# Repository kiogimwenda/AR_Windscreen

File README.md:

# AR_Windscreen

**AR-Assisted Semi-Autonomous Driving System** — a retrofit driver-support platform centered on
precision, sensor-fused AR navigation and force-limited collision-avoidance braking.

The system fuses camera, LiDAR, GPS, IMU and OBD-II data into a real-time model of the road ahead,
renders that understanding as a road-locked augmented-reality overlay on the vehicle's forward view,
and — through a dedicated STM32 sensor/actuator hub — can trigger indicators, lights and a
force-limited brake-pedal actuation when a collision risk crosses a defined threshold.

## Safety

This project has one hard rule that overrides every other design consideration:

> The brake actuator must never be able to exert more force than a driver's foot can override, must
> never disconnect or block the driver's own pedal linkage, and must default to fully released/inert
> on any fault, timeout, link loss, or ambiguous state.

The host laptop never drives actuation hardware directly — it sends a bounded *request* to the hub,
and the hub's firmware enforces the real ceiling, independent of host software correctness. A
physical kill switch removes actuator power independent of software, and the hub's watchdog releases
the actuator within 200 ms of host link loss.

See `docs/BUILD_GUIDE.md` Part 0 and Part 9 for the full safety design.

## Layout

| Path | Contents |
|---|---|
| `docs/` | Build guide, design decisions, progress log, architecture, report and presentation sources |
| `firmware/sensor_actuator_hub/` | STM32 / FreeRTOS firmware — the only component with direct electrical access to the vehicle |
| `host/` | Laptop-side C++ application: perception, fusion, decision, navigation, rendering |
| `tools/bench_rig/` | Bench-test instrumentation and offline replay harness |
| `cmake/` | Custom CMake find-modules (TensorRT) |

## Documentation

- `docs/BUILD_GUIDE.md` — the full implementation specification this project is built from
- `docs/decisions.md` — running log of implementation choices made under ambiguity
- `docs/progress-log.md` — dated, per-task record of work completed
- `docs/architecture/system-architecture.md` — as-built architecture

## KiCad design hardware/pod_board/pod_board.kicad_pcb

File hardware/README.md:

# Hardware

The custom hardware of the two-box hub: `docs/BUILD_GUIDE.md` Part 4.8 is the design, Part 14
Phase 12B the plan.

| Directory | Contents | Status (2026-10-06) |
|---|---|---|
| `gen/` | The board descriptions, the power board's drawing, and the tools that turn them into KiCad files and check them | Done |
| `pod_board/` | KiCad 10 project: STM32F405RGT6, 8 MHz crystal, USB-C, diode-OR'd 5 V to 3.3 V, IMU / GNSS / gesture / SWD / ELM327 headers, status LEDs, DB-25 with series resistors and input filters. 4-layer. | Schematic done, ERC clean, cross-checked; **placed** (77 parts, 0 DRC errors, matches the schematic); **routing to do** (`LAYOUT_GUIDE.md`) |
| `power_board/` | KiCad 10 project: 12 V fuse, TVS and reverse-polarity diode; TPS54360 5 V (TI reference design); 3.3 V; 74HCT244 buffer; BTS7960 and ACS712 module headers; magnet and relay MOSFETs with flyback diodes; fail-safe pull-downs; SN65HVD230 CAN; presence MOSFET; PC817 brake-light input; terminals for the kill relay, E-stop, relays, actuator, LiDAR and OBD lead; DB-25. 2-layer, 2 oz. | Schematic done, ERC clean, cross-checked; **placed** (82 parts, 0 DRC errors, matches the schematic); **routing to do** (`LAYOUT_GUIDE.md`) |
| `enclosures/` | OpenSCAD: LiDAR roof mount, power-box chassis and box drilling templates; shared board outlines (`common/boards.scad`). See its README. | LiDAR mount and power box designed; pod, E-stop and gesture puck wait for the parts and the car |

Each board folder also has `<board>.pdf` (the schematic, for reading without KiCad) and
`<board>_bom.csv` (parts grouped by value and footprint).

## How the schematics are made and checked

```bash
hardware/gen/check.sh
```
1. `gen/generate.py` writes both `.kicad_sch` files from `gen/pod_board.py` and
   `gen/power_board.py`. Each part names its KiCad symbol, footprint and value and maps **pin
   numbers to net names**; the generator copies the real library symbols in.
   - **Both boards are drawn (2026-10-07).** `gen/power_board_drawing.py` places every part by hand
     on one of eight function sheets (12 V input, 5 V converter, 3.3 V and feeds, brake actuator,
     signal relays, CAN, status inputs, DB-25), and `gen/kisheet.py` routes **real wires** between
     the pins, puts power symbols on power pins, names each net with a label, and draws a root
     sheet that is the **block diagram**: one box per sheet, the cable signals wired between them.
     Open `power_board.kicad_pro`, start on the block diagram, double-click a box to enter it.
     `gen/pod_board_drawing.py` does the same for the pod: power, USB-C, the MCU (in the middle,
     every pin straight out to a port), sensors and local connectors, status LEDs, and the cable
     interface (series resistors, pull-ups and filters fanning in to the DB-25 without a crossing).
2. KiCad's ERC must report **0 violations**. For each drawn board, the label-only version is also
   generated (in a scratch directory) and `gen/compare_nets.py` requires the two netlists to be
   **identical**: same parts, values and footprints, every net joining the same pins under the
   same name. The drawing therefore cannot have changed the circuit. The wire router never lets two
   nets touch; a wire may only cross another at right angles over a plain run (no dot, no
   connection), never at a bend, pin or junction.
3. `gen/check_nets.py` reads the exported netlists and verifies, against the sources of truth:
   - every pin in `firmware/.../Config.h` is on the right STM32 pin of the pod board;
   - every DB-25 pin on both boards matches the table in BUILD_GUIDE 4.8.3 (parsed from the guide);
   - pod: each cable line passes through a series resistor; inputs read safe when unplugged;
   - power board: every pod-driven line is pulled to its safe state (Part 4.8.4's rule);
   - no misspelt single-connection nets; no pin in two nets (two parts sharing a reference,
     which KiCad's ERC does not report); every footprint exists in KiCad's library.

   It was tested by breaking the design on purpose (a relay moved to the wrong MCU pin, a
   pull-down removed, two cable pins swapped); each was caught.

**Change the design in `gen/*.py`, never only in KiCad's editor**, then run `check.sh`. Edits made
only in the `.kicad_sch` are overwritten by the next generation. (Once layout starts, the
schematic can be frozen and edited in KiCad directly; then stop regenerating and keep running the
netlist check: export the netlist from KiCad and run `check_nets.py` on it.)

## Choices made during schematic capture (see also decisions.md)

- **Reverse polarity: a B560C Schottky, not a P-MOSFET.** SOT-23 P-MOSFETs are rated −30 V, too
  close to the TVS's ~39 V clamp. The diode drops ~0.6 V (~1 W at 2 A) and needs no gate circuit.
- **5 V converter: TI's TPS54360 reference design, unchanged** (datasheet SLVSBB4G, Figure 34):
  600 kHz, 8.2 µH, B560C, 2 × 47 µF, compensation 13.0 k / 6800 p / 39 p, start 8 V / stop 6.25 V.
  Copying a validated design is the right call for a first board; it is rated well beyond our
  ~1 A load.
- **Relays and magnet: logic-level MOSFETs driven straight from the cable lines** (AO3400A turns
  fully on at 2.5 V); the 74HCT244 buffers only the BTS7960 module's three 5 V inputs.
- **Back-powering:** each pod output has a 1 k series resistor (330 Ω on CAN_TX for its 500 kbit/s
  edges), so a pod running on USB cannot push more than ~3 mA per line into an unpowered box.
- **Module headers are placeholders for breakouts** (BNO085, NEO-M8N): the pin order on `J2` and
  `J3` of the pod board must be matched to the actual breakouts bought **before layout**.

## What remains for Phase 12B (Ian's work)

**Both boards are placed (2026-10-08): routing, finishing and ordering remain, step by step in
[`LAYOUT_GUIDE.md`](LAYOUT_GUIDE.md).** `gen/layout.sh` built each `.kicad_pcb` from the board
descriptions: every footprint from KiCad's library, each pad on its net (from KiCad's own
netlist), placed per `gen/placement.py` (each position with its reason, listed in
`<board>/placement.md`, pictured in `<board>/placement.png`), linked to its schematic symbol, the
net classes and fab rules (`gen/pcb_rules.py`, track widths from IPC-2221) and the copper planes
in place; then KiCad's DRC with the schematic-parity check: 0 errors, exact parity. The schematic
generator now gives every object a deterministic id, so the links survive regeneration and the
files only change when the design does.

The notes below are the layout principles the placement follows (and the guide expands).

**Pod board (4-layer: signal / ground / power / signal).**
- Decoupling capacitors (C3–C9) at their VDD pins, each with its own via to the ground plane.
  VCAP capacitors (C10, C11) right at pins 31 and 47.
- Crystal (Y1, C12, C13) within ~5 mm of PH0/PH1, nothing routed underneath, guard with ground.
- USB D+/D− as a matched pair (~90 Ω differential), short, the ESD chip (U4) right at the socket.
- The GNSS breakout at the board edge that faces the glass, away from the MCU and the USB; keep
  the ground plane unbroken under it.
- The IMU breakout on standoffs at a fixed, known orientation (record it: Part 12.2.2 calibrates
  it, but a sensible starting orientation makes the calibration easy to check).
- DB-25 at one end, the series resistors and input filters right behind it.
- Status LEDs on the edge that faces the driver.

**Power board (2-layer, 2 oz copper).**
- The TPS54360's power loop is the critical path: input capacitors (C21, C22), the IC, the catch
  diode (D13) and the inductor (L1) as close together as possible, the SW node small (it is the
  board's noise source), the feedback divider (R44, R45) away from L1 and the SW node. Follow the
  datasheet's layout example (its "Layout" section) closely.
- Wide traces or pours for the 12 V input, the actuator rail (ACT_12V) and the relay coils' +12 V;
  the actuator's heavy current itself runs in wire on the BTS7960 module, not on this board.
- Fuse holders and terminal blocks along the edges, grouped by what they connect to (12 V in,
  actuator side, car-wiring side).
- The SN65HVD230 and its ESD diode (D20) right at the OBD terminal block.
- The 10 k pull-downs close to the DB-25, so the lines are defined as soon as they enter the board.

**Then:** DRC clean, a 1:1 paper print to check every footprint against the real part, Gerbers,
order (JLCPCB / PCBWay), assemble, and bring up with Part 4.7 before the bench gate is re-run on
this hardware (three consecutive passes of all six items).

## Board outlines: the one constraint shared with the enclosures

```bash
python3 hardware/gen/outlines.py           # --force to overwrite a .kicad_pcb already being laid out
```
`gen/outlines.py` holds each board's size, corner radius, M3 mounting holes and the positions of
its edge connectors (DB-25, USB-C, fuses, terminal blocks, LEDs, headers). It writes the starter
`<board>.kicad_pcb` (outline on Edge.Cuts, hole positions on User.Drawings, connector boxes on
User.Comments: place H1–H4 and the connectors on them) and `enclosures/common/boards.scad`, which
the enclosure models include. Pod board 70 × 53 mm, 4 layers; power board 95 × 66 mm, 2 layers (compacted 2026-10-08 from 80 × 55 and 110 × 80; the power board 5 mm wider again on 2026-10-09 for its silkscreen labels).
If a layout needs a change, change it there and regenerate both. The starter files passed KiCad's
DRC with no errors.

**Placed and routed (2026-10-09):** `gen/layout.sh` places every part (`gen/placement.py`, with
each position's reason and the silkscreen names), `gen/route.sh` routes both boards to the
specification and keeps a board only with 0 unconnected, 0 DRC errors and exact schematic parity,
and `gen/routespec.sh` checks what the DRC cannot (planes, crystal, converter, widths). How it was
done and how to review it: `LAYOUT_GUIDE.md`.

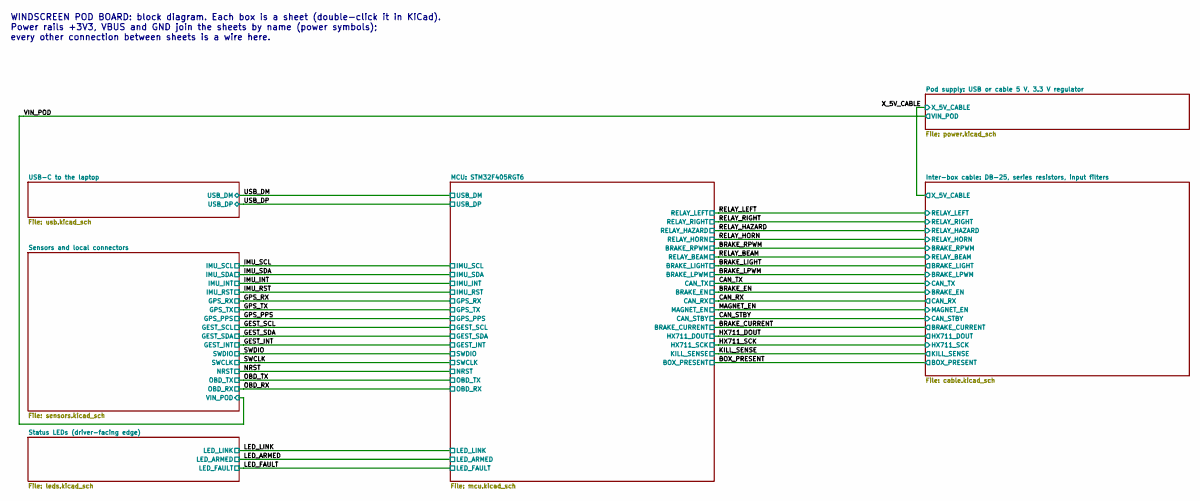
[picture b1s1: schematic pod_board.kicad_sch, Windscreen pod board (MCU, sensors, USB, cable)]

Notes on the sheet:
WINDSCREEN POD BOARD: block diagram. Each box is a sheet (double-click it in KiCad). Power rails +3V3, VBUS and GND join the sheets by name (power symbols); every other connection between sheets is a wire here.

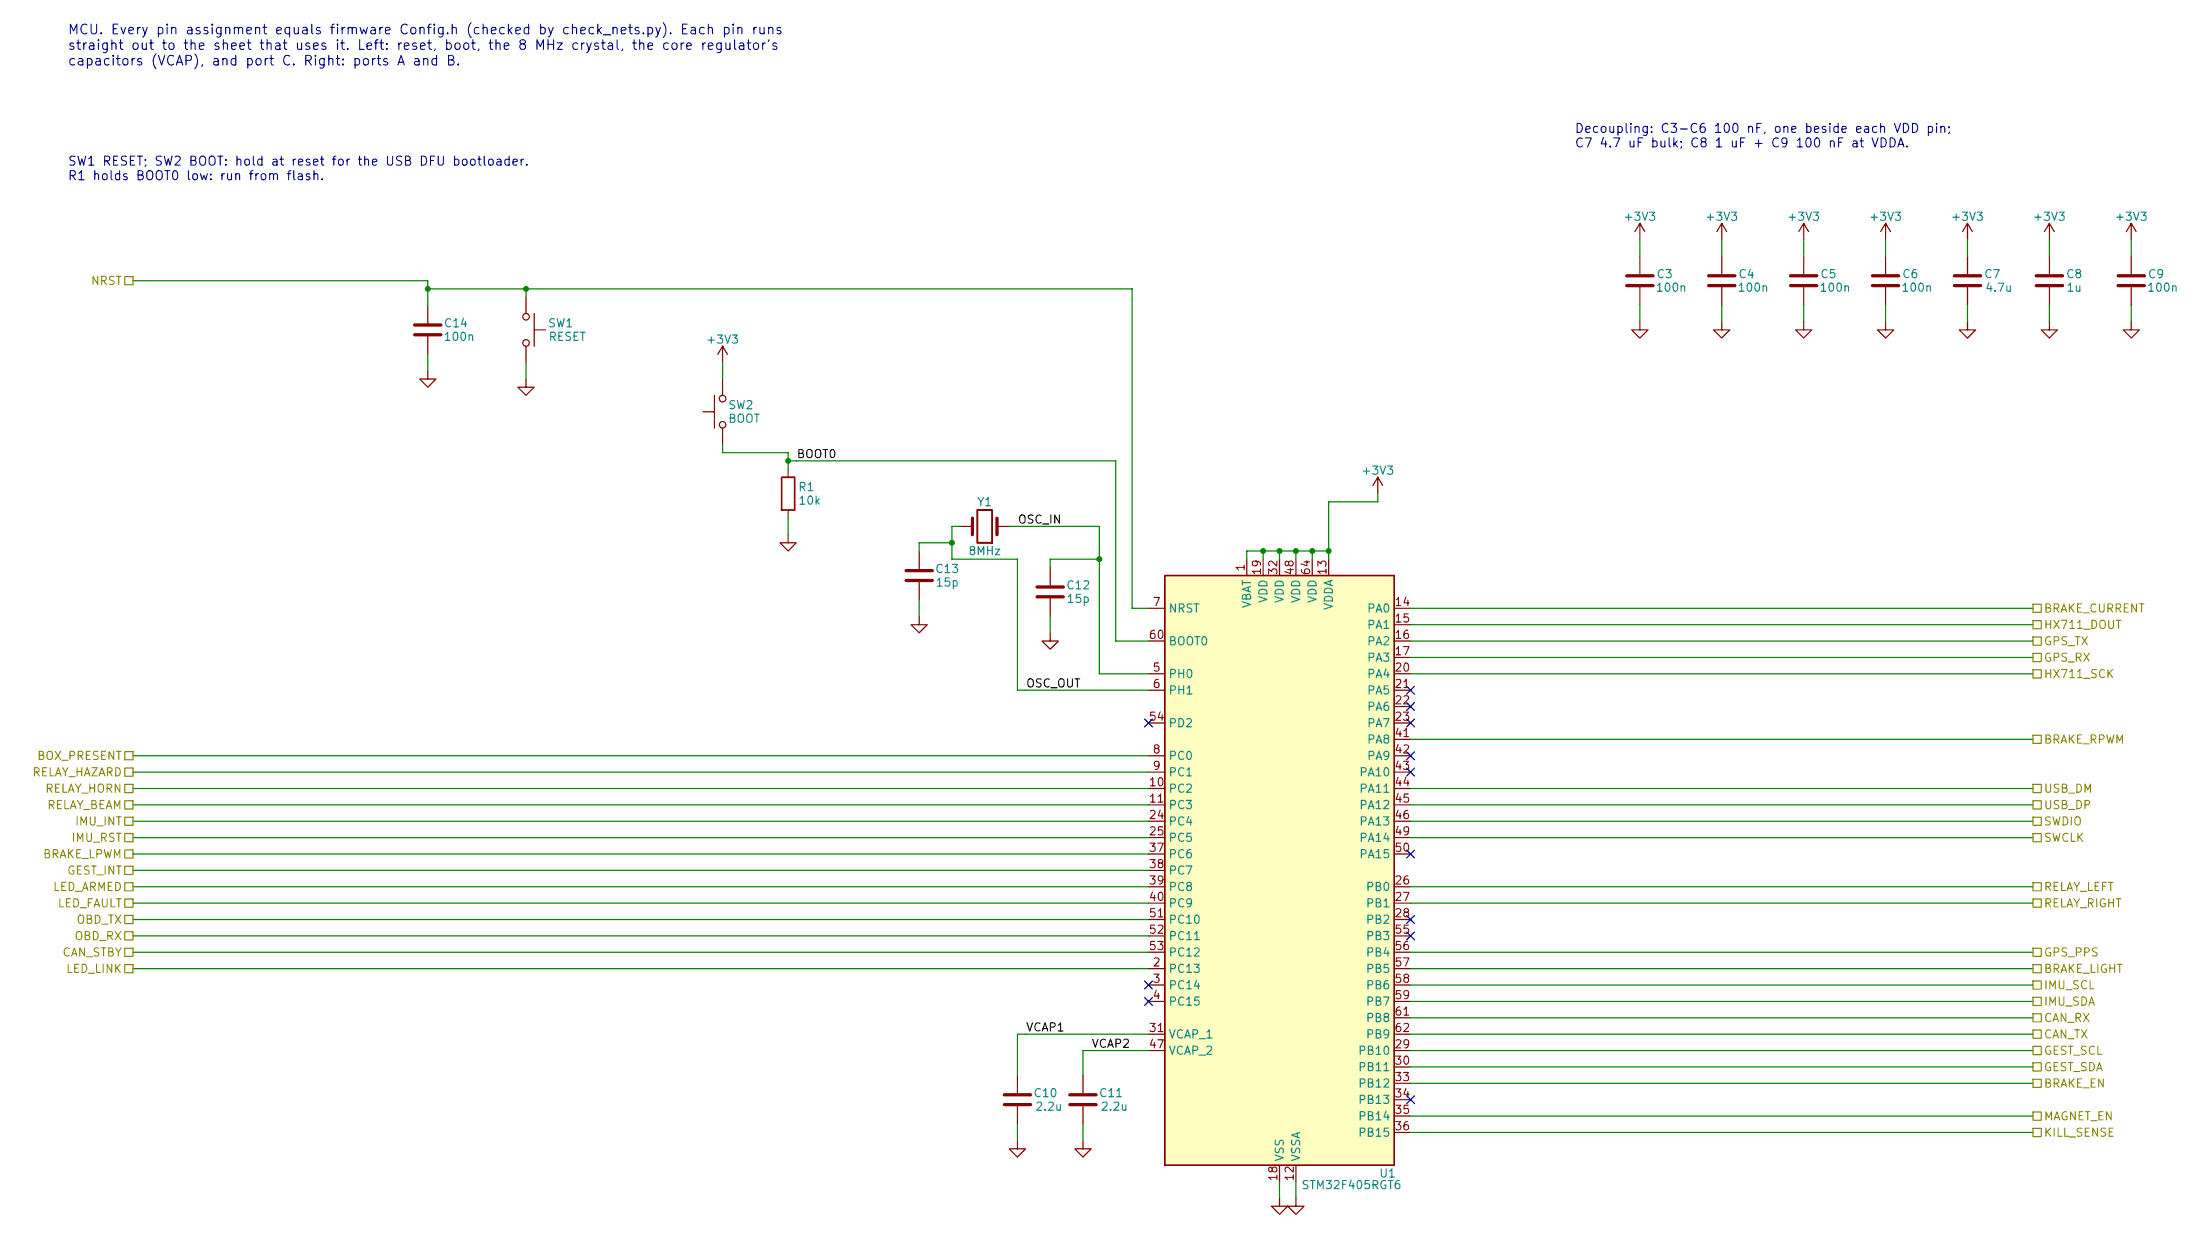
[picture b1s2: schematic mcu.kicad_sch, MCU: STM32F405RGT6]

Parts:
C3, C4, C5, C6, C9, C14: 100n; C_0805_2012Metric
C7: 4.7u; C_1206_3216Metric
C8: 1u; C_0805_2012Metric
C10, C11: 2.2u; C_0805_2012Metric
C12, C13: 15p; C_0805_2012Metric
R1: 10k; R_0805_2012Metric
SW1: RESET; SW_SPST_EVQP7C
SW2: BOOT; SW_SPST_EVQP7C
U1: STM32F405RGT6; LQFP-64_10x10mm_P0.5mm
Y1: 8MHz; Crystal_SMD_HC49-SD

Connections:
+3V3: C3.1, C4.1, C5.1, C6.1, C7.1, C8.1, C9.1, SW2.2, U1.1 (VBAT), U1.13 (VDDA), U1.19 (VDD), U1.32 (VDD), U1.48 (VDD), U1.64 (VDD); also elsewhere on the board
/BOX_PRESENT: U1.8 (PC0); also elsewhere on the board
/BRAKE_CURRENT: U1.14 (PA0); also elsewhere on the board
/BRAKE_EN: U1.33 (PB12); also elsewhere on the board
/BRAKE_LIGHT: U1.57 (PB5); also elsewhere on the board
/BRAKE_LPWM: U1.37 (PC6); also elsewhere on the board
/BRAKE_RPWM: U1.41 (PA8); also elsewhere on the board
/CAN_RX: U1.61 (PB8); also elsewhere on the board
/CAN_STBY: U1.53 (PC12); also elsewhere on the board
/CAN_TX: U1.62 (PB9); also elsewhere on the board
/GEST_INT: U1.38 (PC7); also elsewhere on the board
/GEST_SCL: U1.29 (PB10); also elsewhere on the board
/GEST_SDA: U1.30 (PB11); also elsewhere on the board
/GPS_PPS: U1.56 (PB4); also elsewhere on the board
/GPS_RX: U1.17 (PA3); also elsewhere on the board
/GPS_TX: U1.16 (PA2); also elsewhere on the board
/HX711_DOUT: U1.15 (PA1); also elsewhere on the board
/HX711_SCK: U1.20 (PA4); also elsewhere on the board
/IMU_INT: U1.24 (PC4); also elsewhere on the board
/IMU_RST: U1.25 (PC5); also elsewhere on the board
/IMU_SCL: U1.58 (PB6); also elsewhere on the board
/IMU_SDA: U1.59 (PB7); also elsewhere on the board
/KILL_SENSE: U1.36 (PB15); also elsewhere on the board
/LED_ARMED: U1.39 (PC8); also elsewhere on the board
/LED_FAULT: U1.40 (PC9); also elsewhere on the board
/LED_LINK: U1.2 (PC13); also elsewhere on the board
/MAGNET_EN: U1.35 (PB14); also elsewhere on the board
/MCU: STM32F405RGT6/BOOT0: R1.1, SW2.1, U1.60 (BOOT0)
/MCU: STM32F405RGT6/OSC_IN: C12.1, U1.5 (PH0), Y1.1
/MCU: STM32F405RGT6/OSC_OUT: C13.1, U1.6 (PH1), Y1.2
/MCU: STM32F405RGT6/VCAP1: C10.1, U1.31 (VCAP_1)
/MCU: STM32F405RGT6/VCAP2: C11.1, U1.47 (VCAP_2)
/NRST: C14.1, SW1.1, U1.7 (NRST); also elsewhere on the board
/OBD_RX: U1.52 (PC11); also elsewhere on the board
/OBD_TX: U1.51 (PC10); also elsewhere on the board
/RELAY_BEAM: U1.11 (PC3); also elsewhere on the board
/RELAY_HAZARD: U1.9 (PC1); also elsewhere on the board
/RELAY_HORN: U1.10 (PC2); also elsewhere on the board
/RELAY_LEFT: U1.26 (PB0); also elsewhere on the board
/RELAY_RIGHT: U1.27 (PB1); also elsewhere on the board
/SWCLK: U1.49 (PA14); also elsewhere on the board
/SWDIO: U1.46 (PA13); also elsewhere on the board
/USB_DM: U1.44 (PA11); also elsewhere on the board
/USB_DP: U1.45 (PA12); also elsewhere on the board
GND: C3.2, C4.2, C5.2, C6.2, C7.2, C8.2, C9.2, C10.2, C11.2, C12.2, C13.2, C14.2, R1.2, SW1.2, U1.12 (VSSA), U1.18 (VSS), U1.63 (VSS); also elsewhere on the board

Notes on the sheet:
MCU. Every pin assignment equals firmware Config.h (checked by check_nets.py). Each pin runs straight out to the sheet that uses it. Left: reset, boot, the 8 MHz crystal, the core regulator's capacitors (VCAP), and port C. Right: ports A and B.
Decoupling: C3-C6 100 nF, one beside each VDD pin; C7 4.7 uF bulk; C8 1 uF + C9 100 nF at VDDA.
SW1 RESET; SW2 BOOT: hold at reset for the USB DFU bootloader. R1 holds BOOT0 low: run from flash.

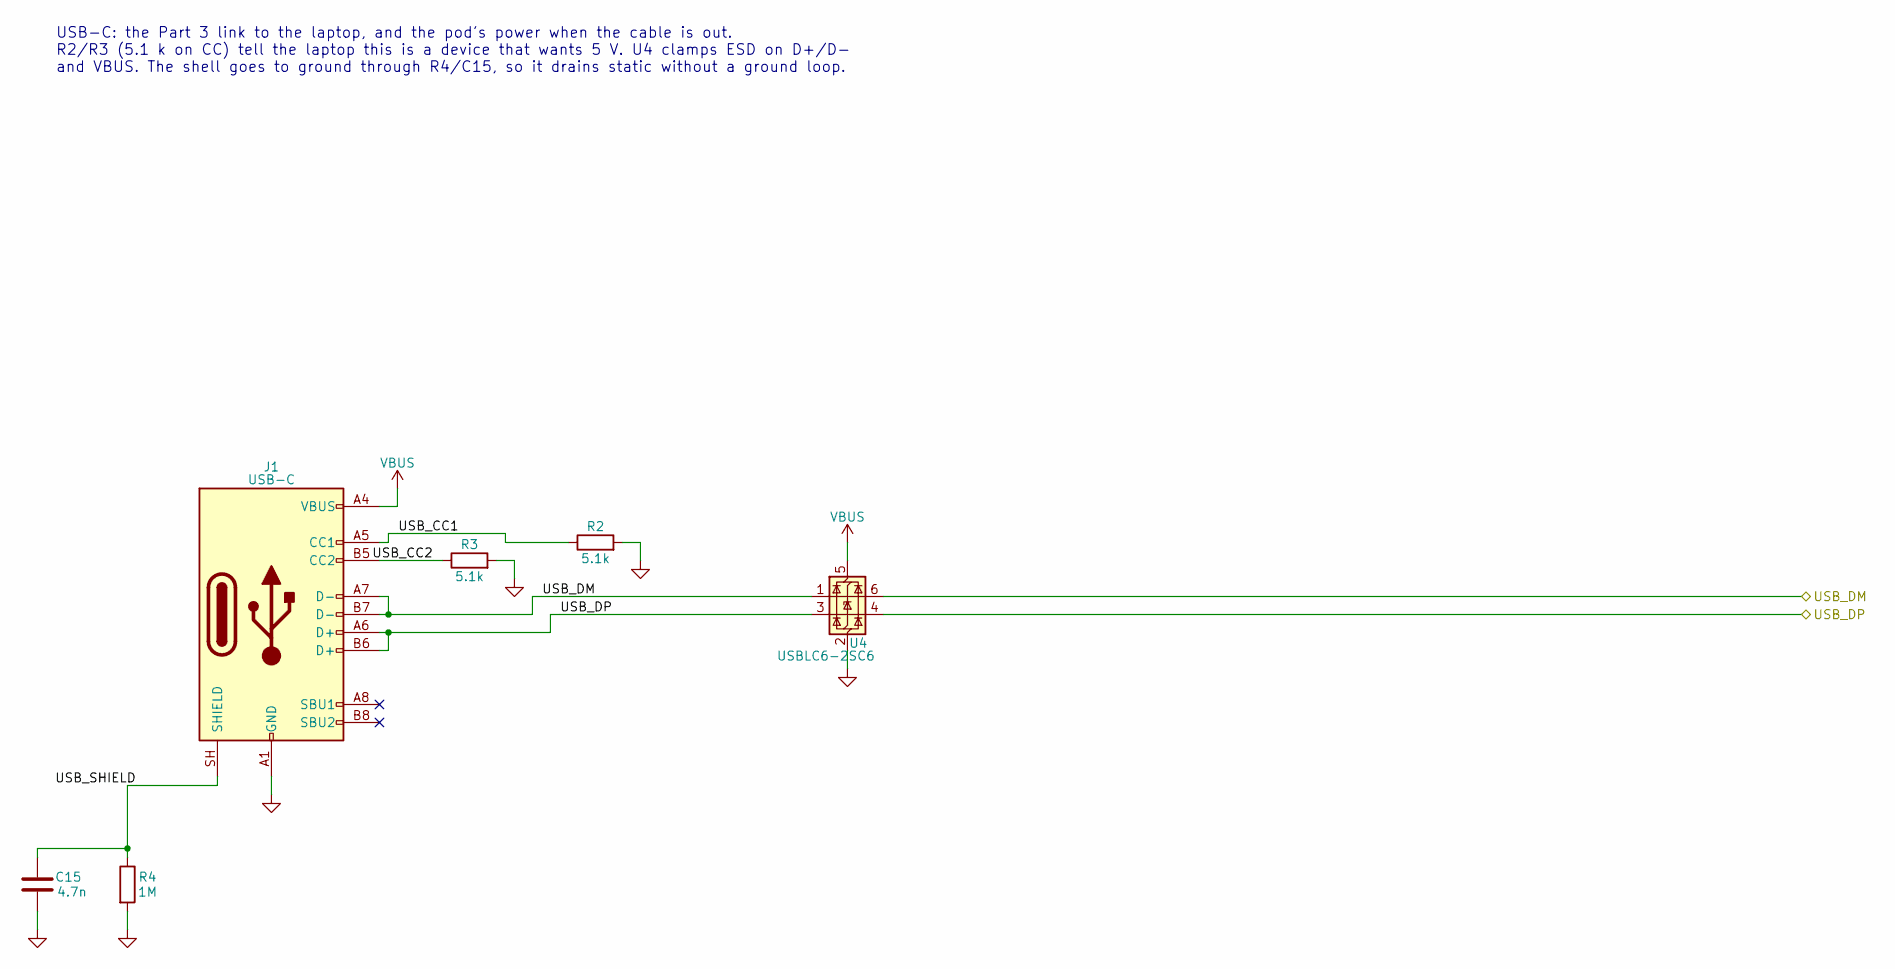
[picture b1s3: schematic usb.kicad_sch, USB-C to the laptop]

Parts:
C15: 4.7n; C_0805_2012Metric
J1: USB-C; USB_C_Receptacle_GCT_USB4105-xx-A_16P_TopMnt_Horizontal
R2, R3: 5.1k; R_0805_2012Metric
R4: 1M; R_0805_2012Metric
U4: USBLC6-2SC6; SOT-23-6

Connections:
/USB-C to the laptop/USB_CC1: J1.A5 (CC1), R2.1
/USB-C to the laptop/USB_CC2: J1.B5 (CC2), R3.1
/USB-C to the laptop/USB_SHIELD: C15.1, J1.SH (SHIELD), R4.1
/USB_DM: J1.A7 (D-), J1.B7 (D-), U4.1 (I/O1), U4.6 (I/O1); also elsewhere on the board
/USB_DP: J1.A6 (D+), J1.B6 (D+), U4.3 (I/O2), U4.4 (I/O2); also elsewhere on the board
GND: C15.2, J1.A1 (GND), J1.A12 (GND), J1.B1 (GND), J1.B12 (GND), R2.2, R3.2, R4.2, U4.2 (GND); also elsewhere on the board
VBUS: J1.A4 (VBUS), J1.A9 (VBUS), J1.B4 (VBUS), J1.B9 (VBUS), U4.5 (VBUS); also elsewhere on the board

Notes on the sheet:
USB-C: the Part 3 link to the laptop, and the pod's power when the cable is out. R2/R3 (5.1 k on CC) tell the laptop this is a device that wants 5 V. U4 clamps ESD on D+/D- and VBUS. The shell goes to ground through R4/C15, so it drains static without a ground loop.

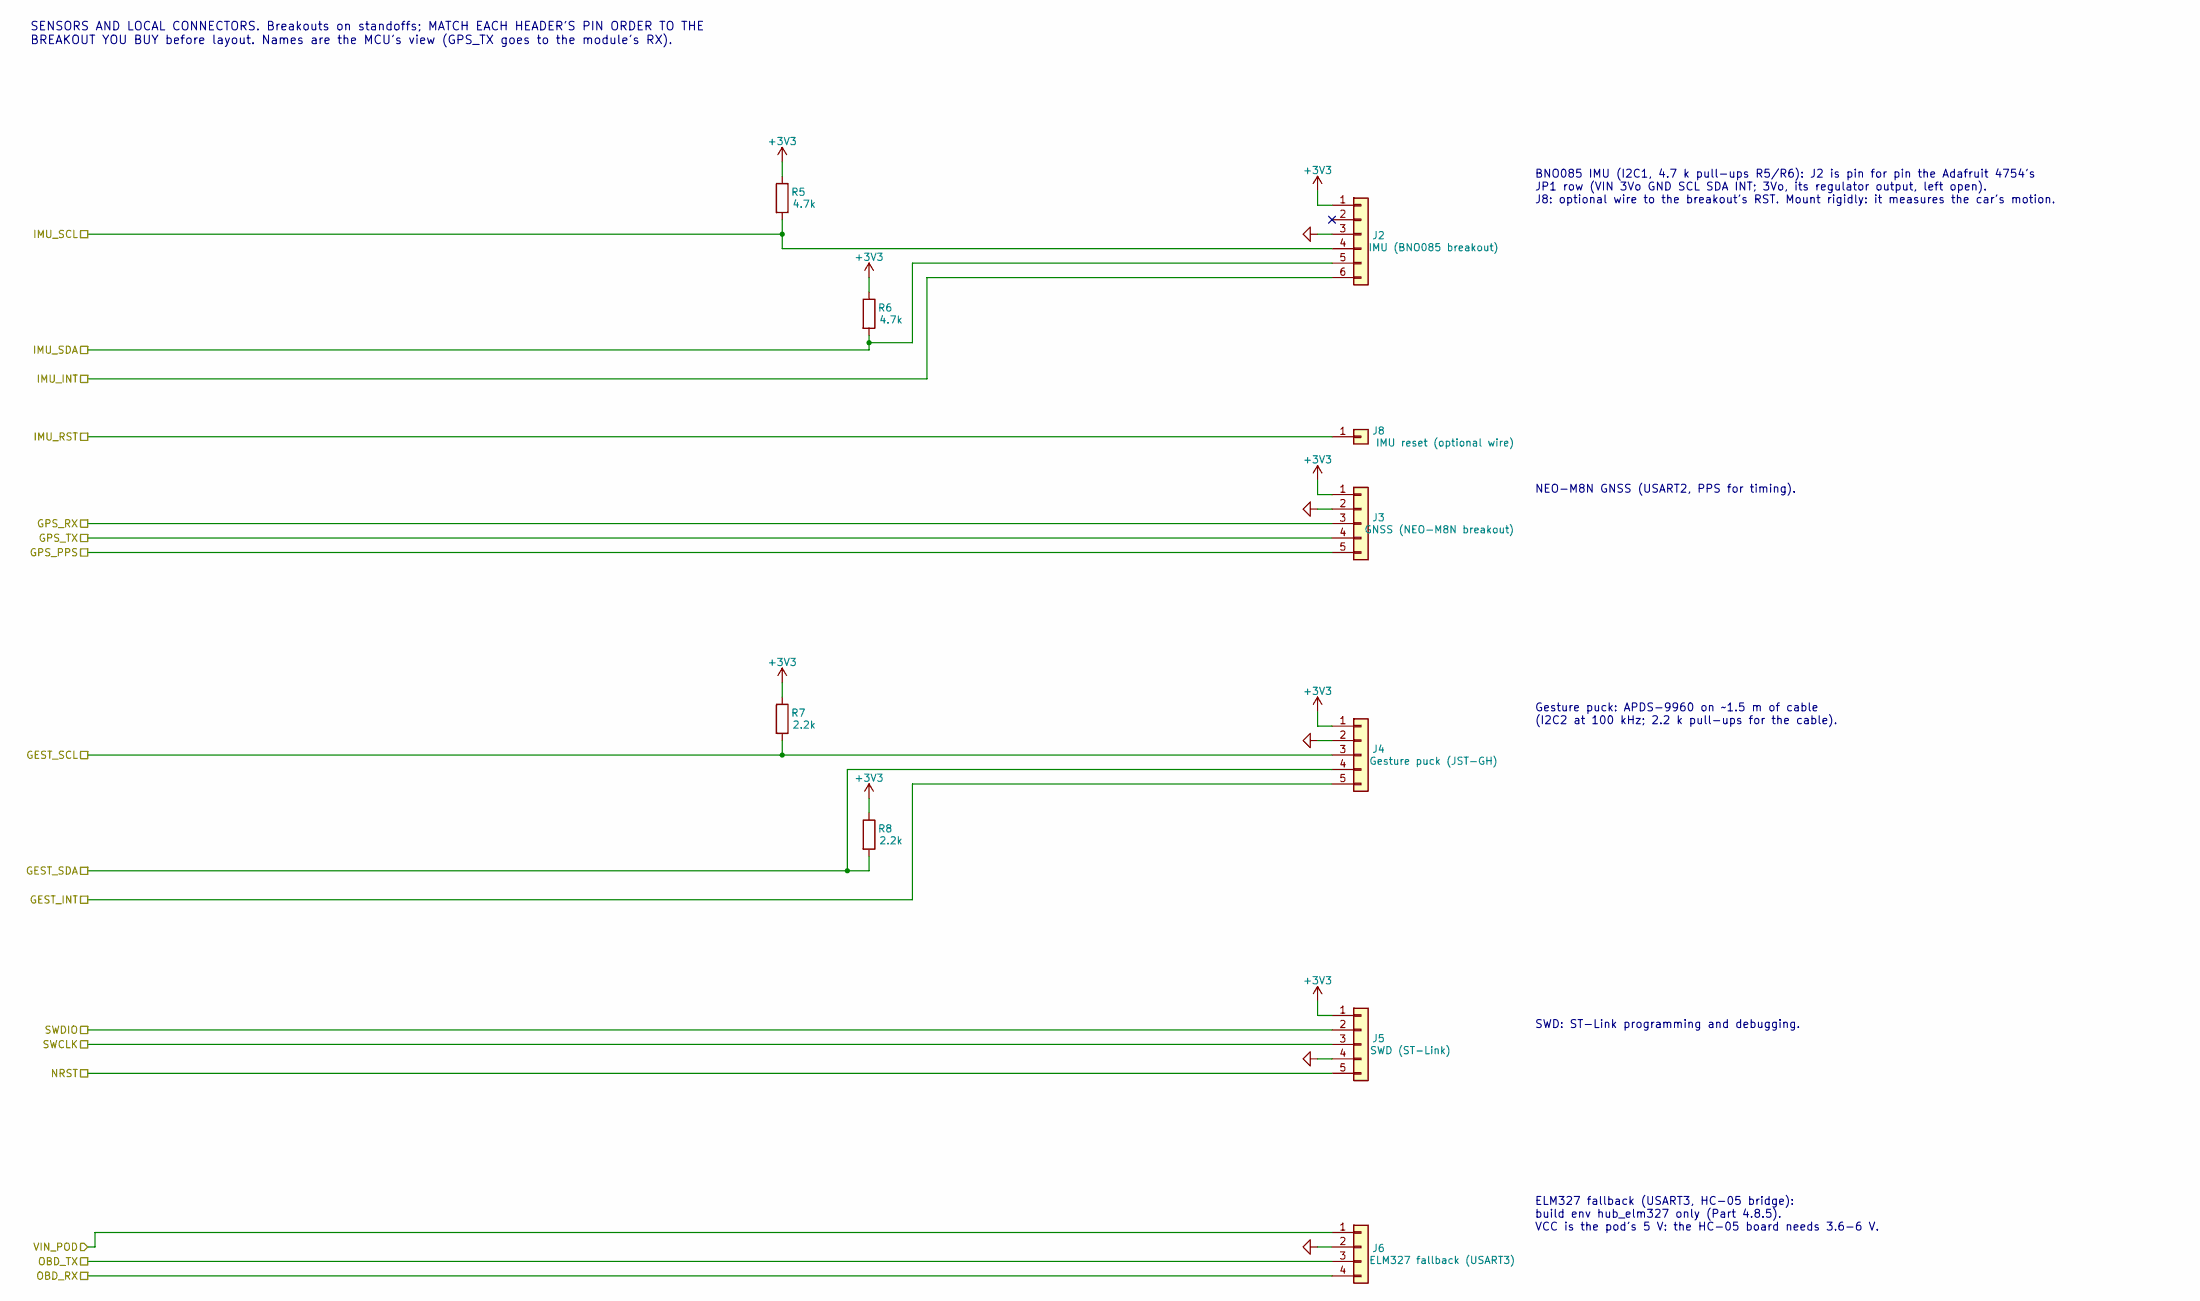
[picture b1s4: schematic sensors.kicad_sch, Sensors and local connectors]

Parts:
J2: IMU (BNO085 breakout); PinHeader_1x06_P2.54mm_Vertical
J3: GNSS (NEO-M8N breakout); PinHeader_1x05_P2.54mm_Vertical
J4: Gesture puck (JST-GH); JST_GH_SM05B-GHS-TB_1x05-1MP_P1.25mm_Horizontal
J5: SWD (ST-Link); PinHeader_1x05_P2.54mm_Vertical
J6: ELM327 fallback (USART3); PinHeader_1x04_P2.54mm_Vertical
J8: IMU reset (optional wire); PinHeader_1x01_P2.54mm_Vertical
R5, R6: 4.7k; R_0805_2012Metric
R7, R8: 2.2k; R_0805_2012Metric

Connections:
+3V3: J2.1, J3.1, J4.1, J5.1, R5.1, R6.1, R7.1, R8.1; also elsewhere on the board
/GEST_INT: J4.5; also elsewhere on the board
/GEST_SCL: J4.3, R7.2; also elsewhere on the board
/GEST_SDA: J4.4, R8.2; also elsewhere on the board
/GPS_PPS: J3.5; also elsewhere on the board
/GPS_RX: J3.3; also elsewhere on the board
/GPS_TX: J3.4; also elsewhere on the board
/IMU_INT: J2.6; also elsewhere on the board
/IMU_RST: J8.1; also elsewhere on the board
/IMU_SCL: J2.4, R5.2; also elsewhere on the board
/IMU_SDA: J2.5, R6.2; also elsewhere on the board
/NRST: J5.5; also elsewhere on the board
/OBD_RX: J6.4; also elsewhere on the board
/OBD_TX: J6.3; also elsewhere on the board
/SWCLK: J5.3; also elsewhere on the board
/SWDIO: J5.2; also elsewhere on the board
/VIN_POD: J6.1; also elsewhere on the board
GND: J2.3, J3.2, J4.2, J5.4, J6.2; also elsewhere on the board

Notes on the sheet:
SENSORS AND LOCAL CONNECTORS. Breakouts on standoffs; MATCH EACH HEADER'S PIN ORDER TO THE BREAKOUT YOU BUY before layout. Names are the MCU's view (GPS_TX goes to the module's RX).
BNO085 IMU (I2C1, 4.7 k pull-ups R5/R6): J2 is pin for pin the Adafruit 4754's JP1 row (VIN 3Vo GND SCL SDA INT; 3Vo, its regulator output, left open). J8: optional wire to the breakout's RST. Mount rigidly: it measures the car's motion.
NEO-M8N GNSS (USART2, PPS for timing).
Gesture puck: APDS-9960 on ~1.5 m of cable (I2C2 at 100 kHz; 2.2 k pull-ups for the cable).
SWD: ST-Link programming and debugging.
ELM327 fallback (USART3, HC-05 bridge): build env hub_elm327 only (Part 4.8.5). VCC is the pod's 5 V: the HC-05 board needs 3.6-6 V.

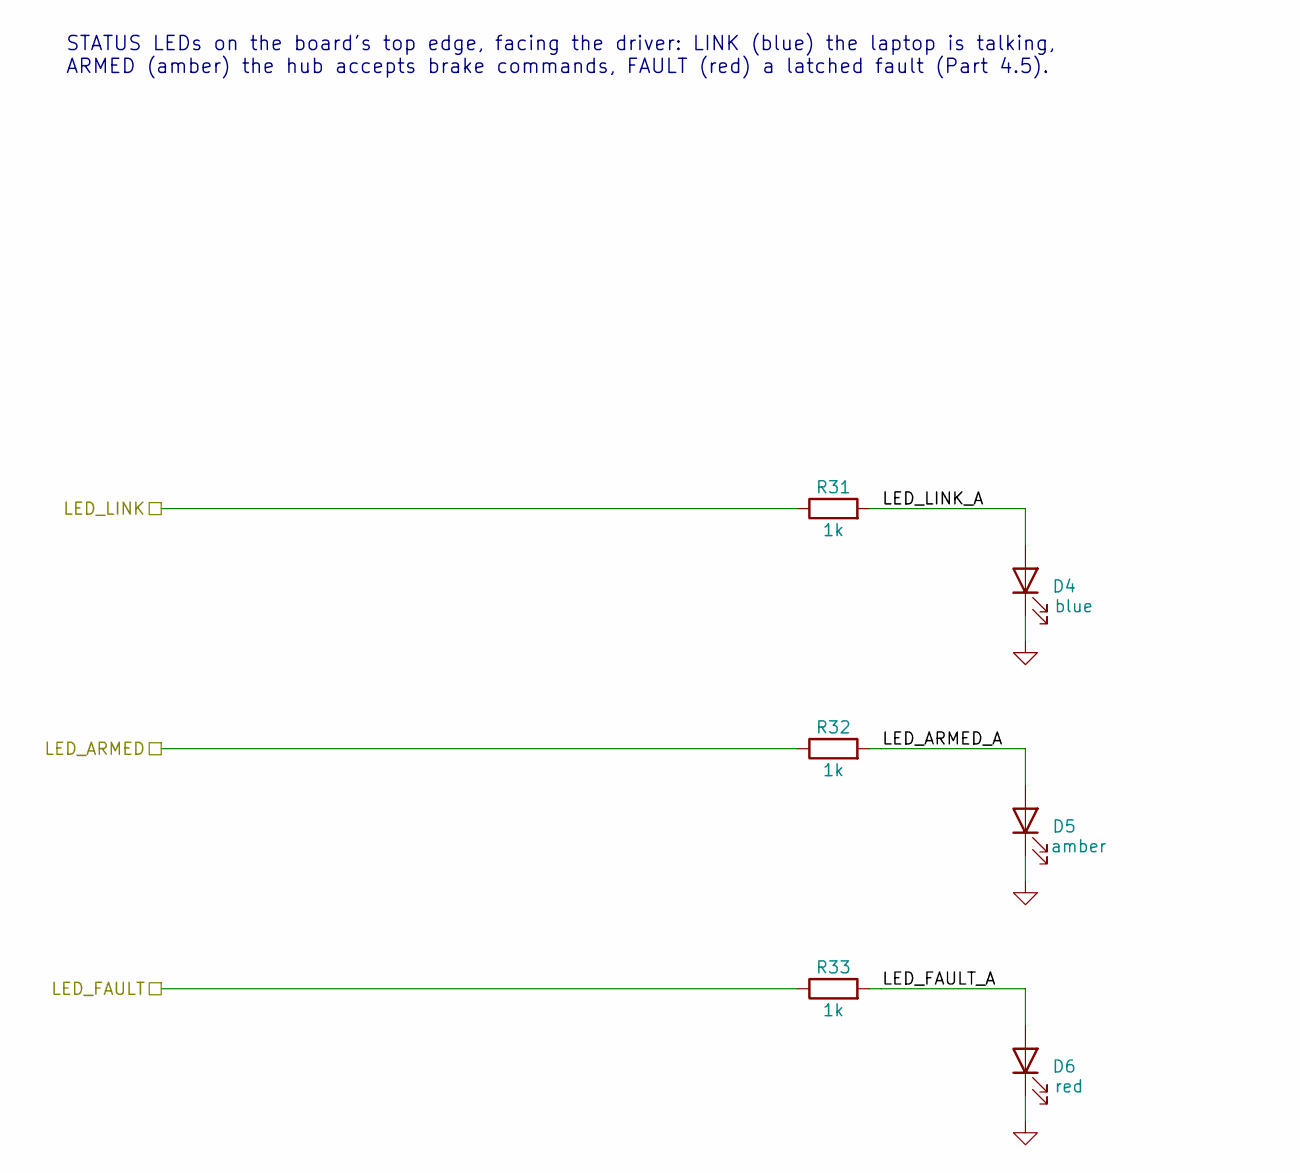
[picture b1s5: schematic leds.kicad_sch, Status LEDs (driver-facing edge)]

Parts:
D4: blue; LED_0805_2012Metric
D5: amber; LED_0805_2012Metric
D6: red; LED_0805_2012Metric
R31, R32, R33: 1k; R_0805_2012Metric

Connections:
/LED_ARMED: R32.1; also elsewhere on the board
/LED_FAULT: R33.1; also elsewhere on the board
/LED_LINK: R31.1; also elsewhere on the board
/Status LEDs (driver-facing edge)/LED_ARMED_A: D5.2 (A), R32.2
/Status LEDs (driver-facing edge)/LED_FAULT_A: D6.2 (A), R33.2
/Status LEDs (driver-facing edge)/LED_LINK_A: D4.2 (A), R31.2
GND: D4.1 (K), D5.1 (K), D6.1 (K); also elsewhere on the board

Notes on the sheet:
STATUS LEDs on the board's top edge, facing the driver: LINK (blue) the laptop is talking, ARMED (amber) the hub accepts brake commands, FAULT (red) a latched fault (Part 4.5).

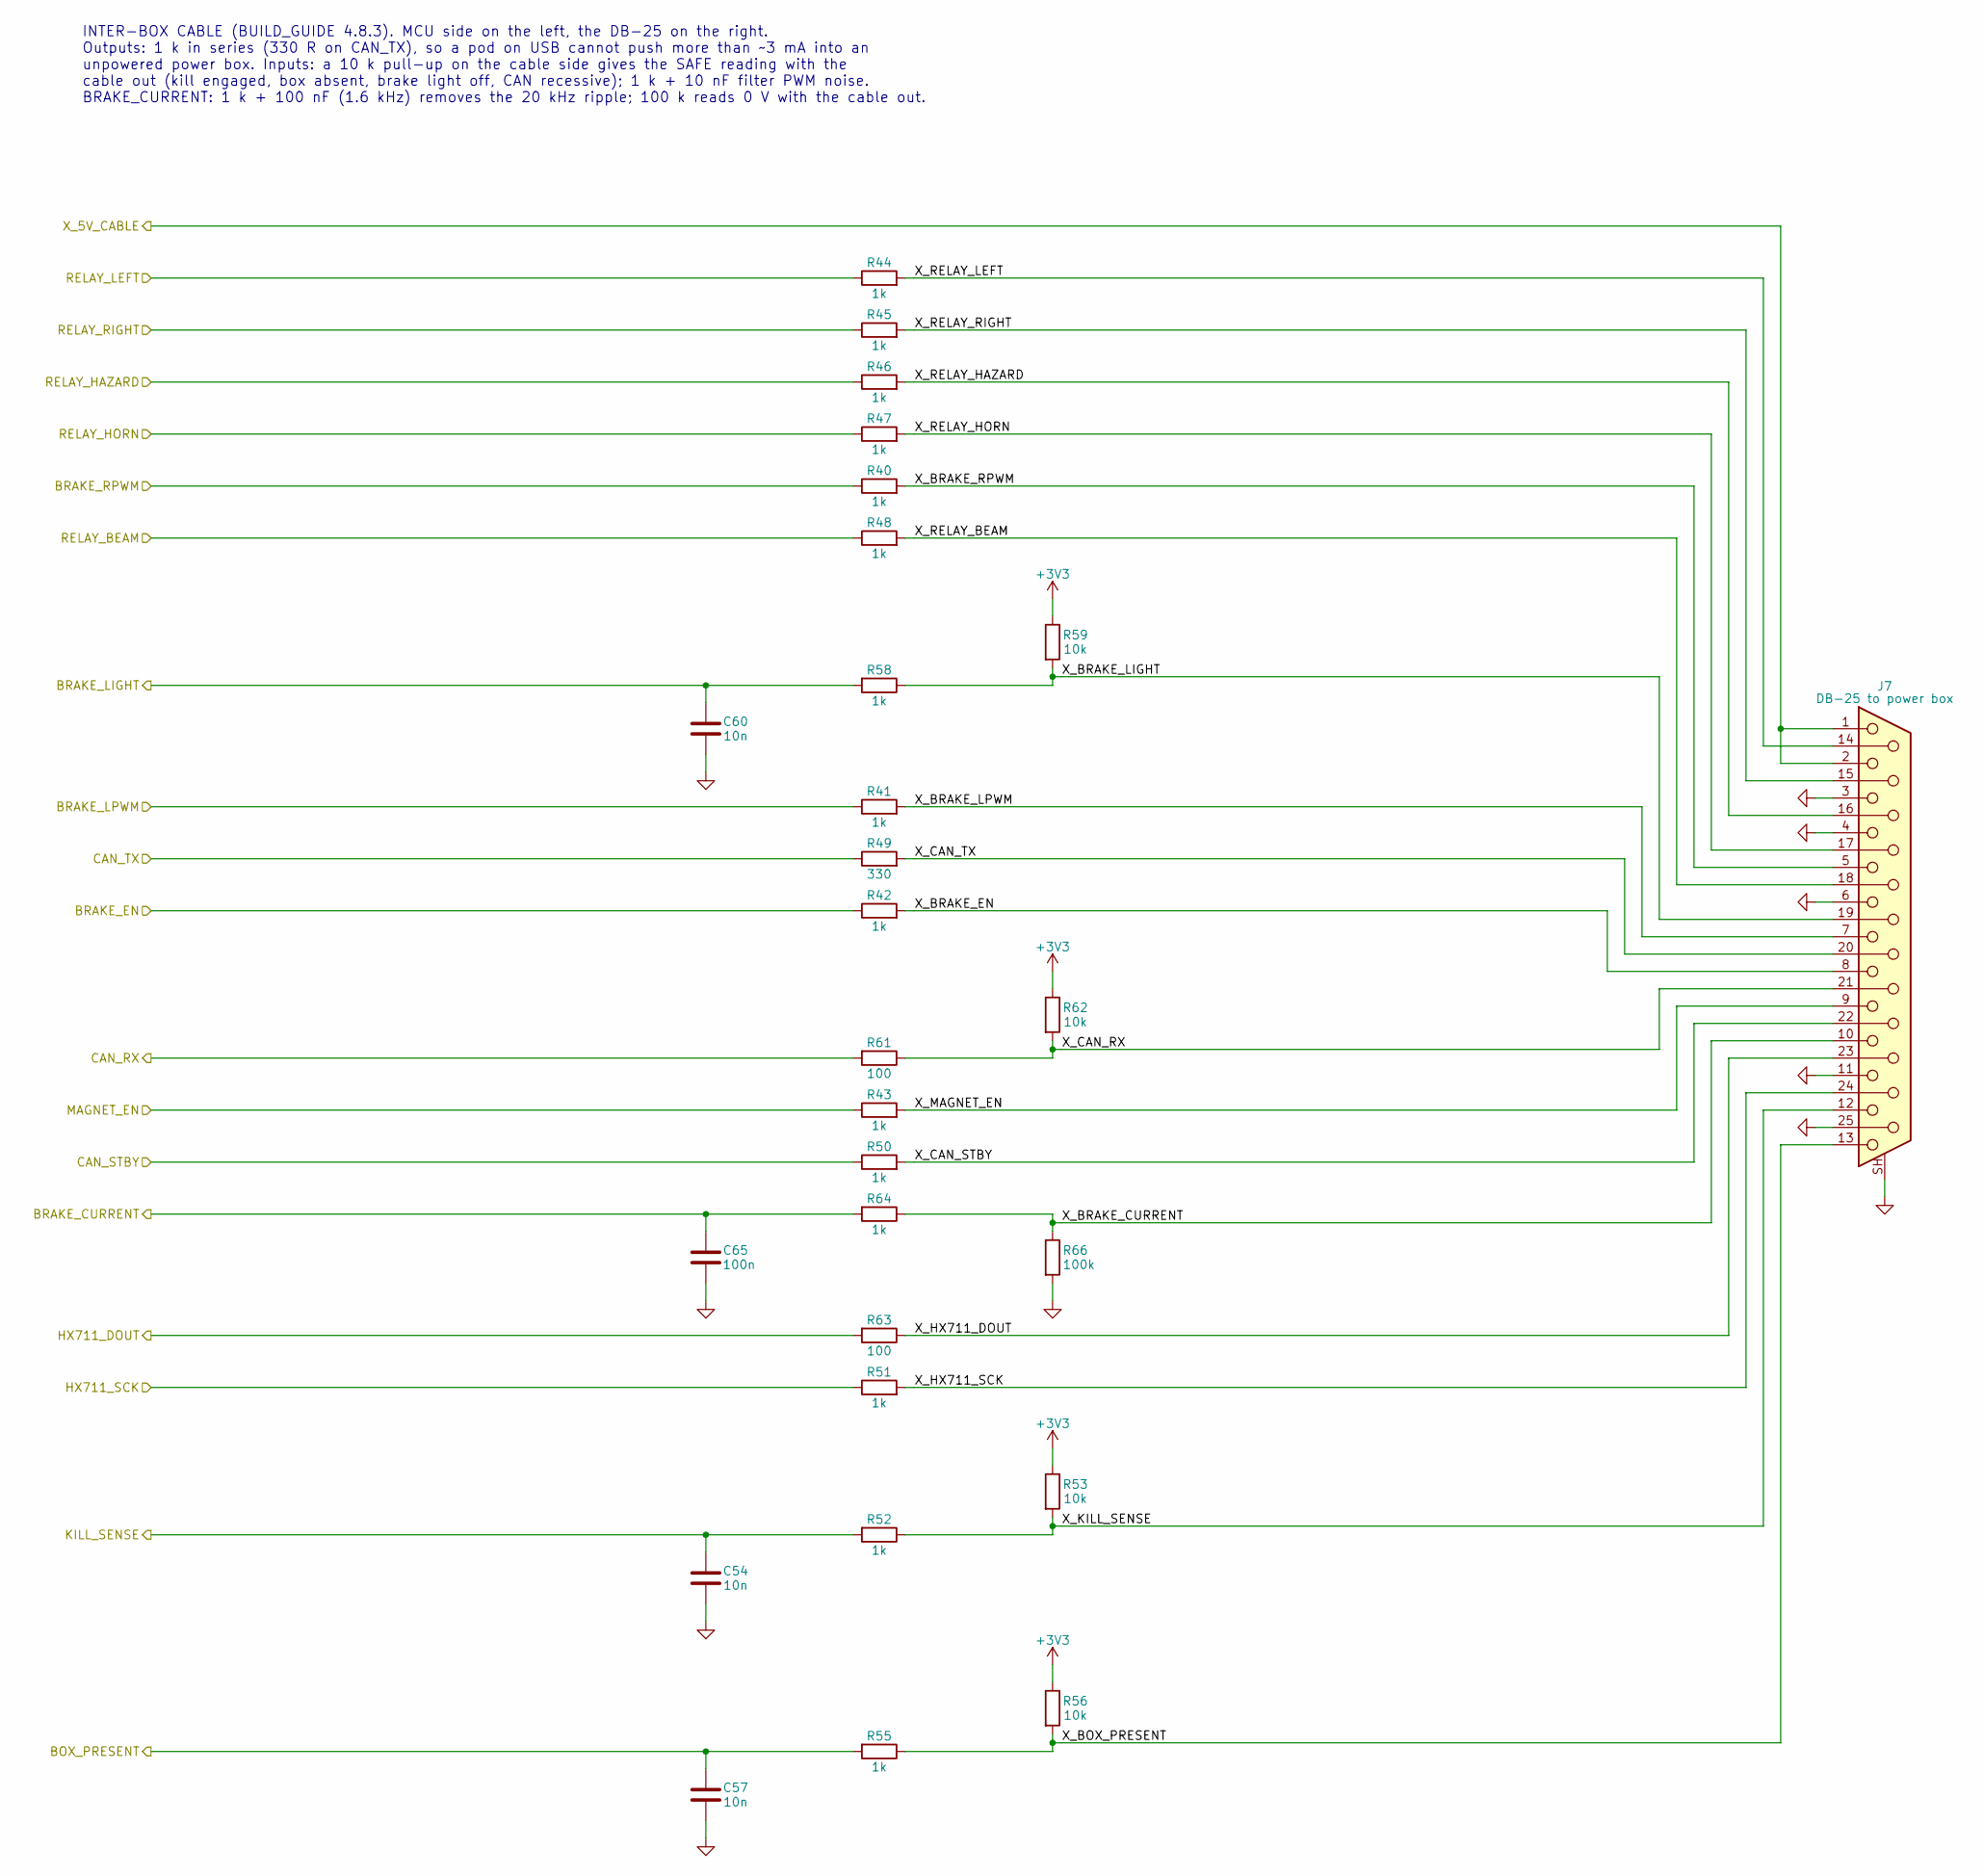
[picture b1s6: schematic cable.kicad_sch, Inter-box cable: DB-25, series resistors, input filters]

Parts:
C54, C57, C60: 10n; C_0805_2012Metric
C65: 100n; C_0805_2012Metric
J7: DB-25 to power box; DSUB-25_Socket_Horizontal_P2.77x2.84mm_EdgePinOffset4.94mm_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
R40, R41, R42, R43, R44, R45, R46, R47, R48, R50, R51, R52, R55, R58, R64: 1k; R_0805_2012Metric
R49: 330; R_0805_2012Metric
R53, R56, R59, R62: 10k; R_0805_2012Metric
R61, R63: 100; R_0805_2012Metric
R66: 100k; R_0805_2012Metric

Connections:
+3V3: R53.1, R56.1, R59.1, R62.1; also elsewhere on the board
/BOX_PRESENT: C57.1, R55.2; also elsewhere on the board
/BRAKE_CURRENT: C65.1, R64.2; also elsewhere on the board
/BRAKE_EN: R42.1; also elsewhere on the board
/BRAKE_LIGHT: C60.1, R58.2; also elsewhere on the board
/BRAKE_LPWM: R41.1; also elsewhere on the board
/BRAKE_RPWM: R40.1; also elsewhere on the board
/CAN_RX: R61.2; also elsewhere on the board
/CAN_STBY: R50.1; also elsewhere on the board
/CAN_TX: R49.1; also elsewhere on the board
/HX711_DOUT: R63.2; also elsewhere on the board
/HX711_SCK: R51.1; also elsewhere on the board
/Inter-box cable: DB-25, series resistors, input filters/X_BOX_PRESENT: J7.13, R55.1, R56.2
/Inter-box cable: DB-25, series resistors, input filters/X_BRAKE_CURRENT: J7.10, R64.1, R66.1
/Inter-box cable: DB-25, series resistors, input filters/X_BRAKE_EN: J7.8, R42.2
/Inter-box cable: DB-25, series resistors, input filters/X_BRAKE_LIGHT: J7.19, R58.1, R59.2
/Inter-box cable: DB-25, series resistors, input filters/X_BRAKE_LPWM: J7.7, R41.2
/Inter-box cable: DB-25, series resistors, input filters/X_BRAKE_RPWM: J7.5, R40.2
/Inter-box cable: DB-25, series resistors, input filters/X_CAN_RX: J7.21, R61.1, R62.2
/Inter-box cable: DB-25, series resistors, input filters/X_CAN_STBY: J7.22, R50.2
/Inter-box cable: DB-25, series resistors, input filters/X_CAN_TX: J7.20, R49.2
/Inter-box cable: DB-25, series resistors, input filters/X_HX711_DOUT: J7.23, R63.1
/Inter-box cable: DB-25, series resistors, input filters/X_HX711_SCK: J7.24, R51.2
/Inter-box cable: DB-25, series resistors, input filters/X_KILL_SENSE: J7.12, R52.1, R53.2
/Inter-box cable: DB-25, series resistors, input filters/X_MAGNET_EN: J7.9, R43.2
/Inter-box cable: DB-25, series resistors, input filters/X_RELAY_BEAM: J7.18, R48.2
/Inter-box cable: DB-25, series resistors, input filters/X_RELAY_HAZARD: J7.16, R46.2
/Inter-box cable: DB-25, series resistors, input filters/X_RELAY_HORN: J7.17, R47.2
/Inter-box cable: DB-25, series resistors, input filters/X_RELAY_LEFT: J7.14, R44.2
/Inter-box cable: DB-25, series resistors, input filters/X_RELAY_RIGHT: J7.15, R45.2
/KILL_SENSE: C54.1, R52.2; also elsewhere on the board
/MAGNET_EN: R43.1; also elsewhere on the board
/RELAY_BEAM: R48.1; also elsewhere on the board
/RELAY_HAZARD: R46.1; also elsewhere on the board
/RELAY_HORN: R47.1; also elsewhere on the board
/RELAY_LEFT: R44.1; also elsewhere on the board
/RELAY_RIGHT: R45.1; also elsewhere on the board
/X_5V_CABLE: J7.1, J7.2; also elsewhere on the board
GND: C54.2, C57.2, C60.2, C65.2, J7.3, J7.4, J7.6, J7.11, J7.25, J7.SH (PAD), R66.2; also elsewhere on the board

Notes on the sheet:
INTER-BOX CABLE (BUILD_GUIDE 4.8.3). MCU side on the left, the DB-25 on the right. Outputs: 1 k in series (330 R on CAN_TX), so a pod on USB cannot push more than ~3 mA into an unpowered power box. Inputs: a 10 k pull-up on the cable side gives the SAFE reading with the cable out (kill engaged, box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
